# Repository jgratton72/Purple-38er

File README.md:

# 🟣 Purple-38er — ZX81+38 Clone (Rev 1.10)

A personal build of the **ZX81+38** clone using purple PCBs and tactile switch keys. This project documents the assembly, troubleshooting, and validation of a modern recreation of the Sinclair ZX81 using standard logic ICs and through-hole components.

---

## 🧰 Project Overview

- **Board Revision**: ZX81+38 Rev 1.10  
- **Design Origin**: Mahjongg’s open-source ZX81+38  
- **Build Variant**: Purple PCB with tactile switch keyboard  
- **Objective**: Achieve reliable boot with “K” prompt, stable composite video, and verified ROM/RAM operation

---

## 🔧 Key Components

| Component        | Value / Type             | Notes                                  |
|------------------|--------------------------|----------------------------------------|
| Crystal          | 13 MHz                   | Required for correct video timing      |
| CPU              | Z80A                     | Clocked at 3.25 MHz (÷4 from crystal)  |
| ROM              | 27C256 OTP EPROM         | One-time programmable; verified in chip tester |
| RAM              | HM62256BLP-7             | Stable operation confirmed             |
| RP2              | 22kΩ bussed network      | Pull-ups for D0–D7; critical for boot  |
| 74HCU04          | Unbuffered inverter      | Required for crystal oscillator        |

---

## 🧪 Troubleshooting Log

- **White Screen / No “K” Prompt**:
  - All chips tested in alternate board—confirmed working  
  - RP2 replaced with 22kΩ bussed network—resolved boot issue  
  - Clock verified: 13 MHz at 74HCU04 pin 2, 3.25 MHz at Z80 pin 6

- **ROM Activity**:
  - /CS and /OE toggling observed  
  - Address and data bus activity confirmed

- **Video Output**:
  - Composite waveform present at RCA jack  
  - Sync stable after oscillator validation

---

## 📝 Build Notes

- All decoupling capacitors (100 nF) installed near ICs  
- Socketed chips reseated during debugging  
- Board now boots reliably with “K” prompt and clean composite output

---

## 📷 Visuals

The `images/` folder contains a detailed visual archive of the design and build process:

| Subfolder            | Description                                                                 |
|----------------------|-----------------------------------------------------------------------------|
| `Assembly/`          | Final integration of keyboard and main PCB into the 3D-printed case         |
| `Case 3D/`           | 3D design views of the enclosure                                            |
| `Case Printed Raw/`  | Photos of the finished, unassembled printed case                            |
| `Keyboard 3D/`       | 3D renderings of the keyboard layout and switch matrix                      |
| `Keyboard Build/`    | Step-by-step documentation of keyboard assembly                             |
| `Keycaps/`           | Design files and visuals for custom keycaps                                 |
| `PCB 3D/`            | 3D views of the main PCB layout and component placement                     |
| `PCB Build/`         | Photo documentation of the main PCB assembly process                        |

---

## 🛠 Assembly Notes

- **USB Power Connector**:  
   Insulate the top of the USB connector to prevent contact with the underside of the tactile switches.

- **Capacitor C9**:  
  Angle C9 flat 90 degrees away from the main board to avoid shorting against the underside of the tactile switches.
  
  ⚠️ These issues caused keyboard failure when the case was closed.

---

## 📚 References

- [ZX81+38 Original Repository](https://github.com/mahjongg2/ZX81plus38)  
- [RevSpace Project Page](https://revspace.nl/ZX81plus38_simple_to_build_ZX-81_clone)  
- [Forum64 Build Threads](https://www.forum64.de)

---

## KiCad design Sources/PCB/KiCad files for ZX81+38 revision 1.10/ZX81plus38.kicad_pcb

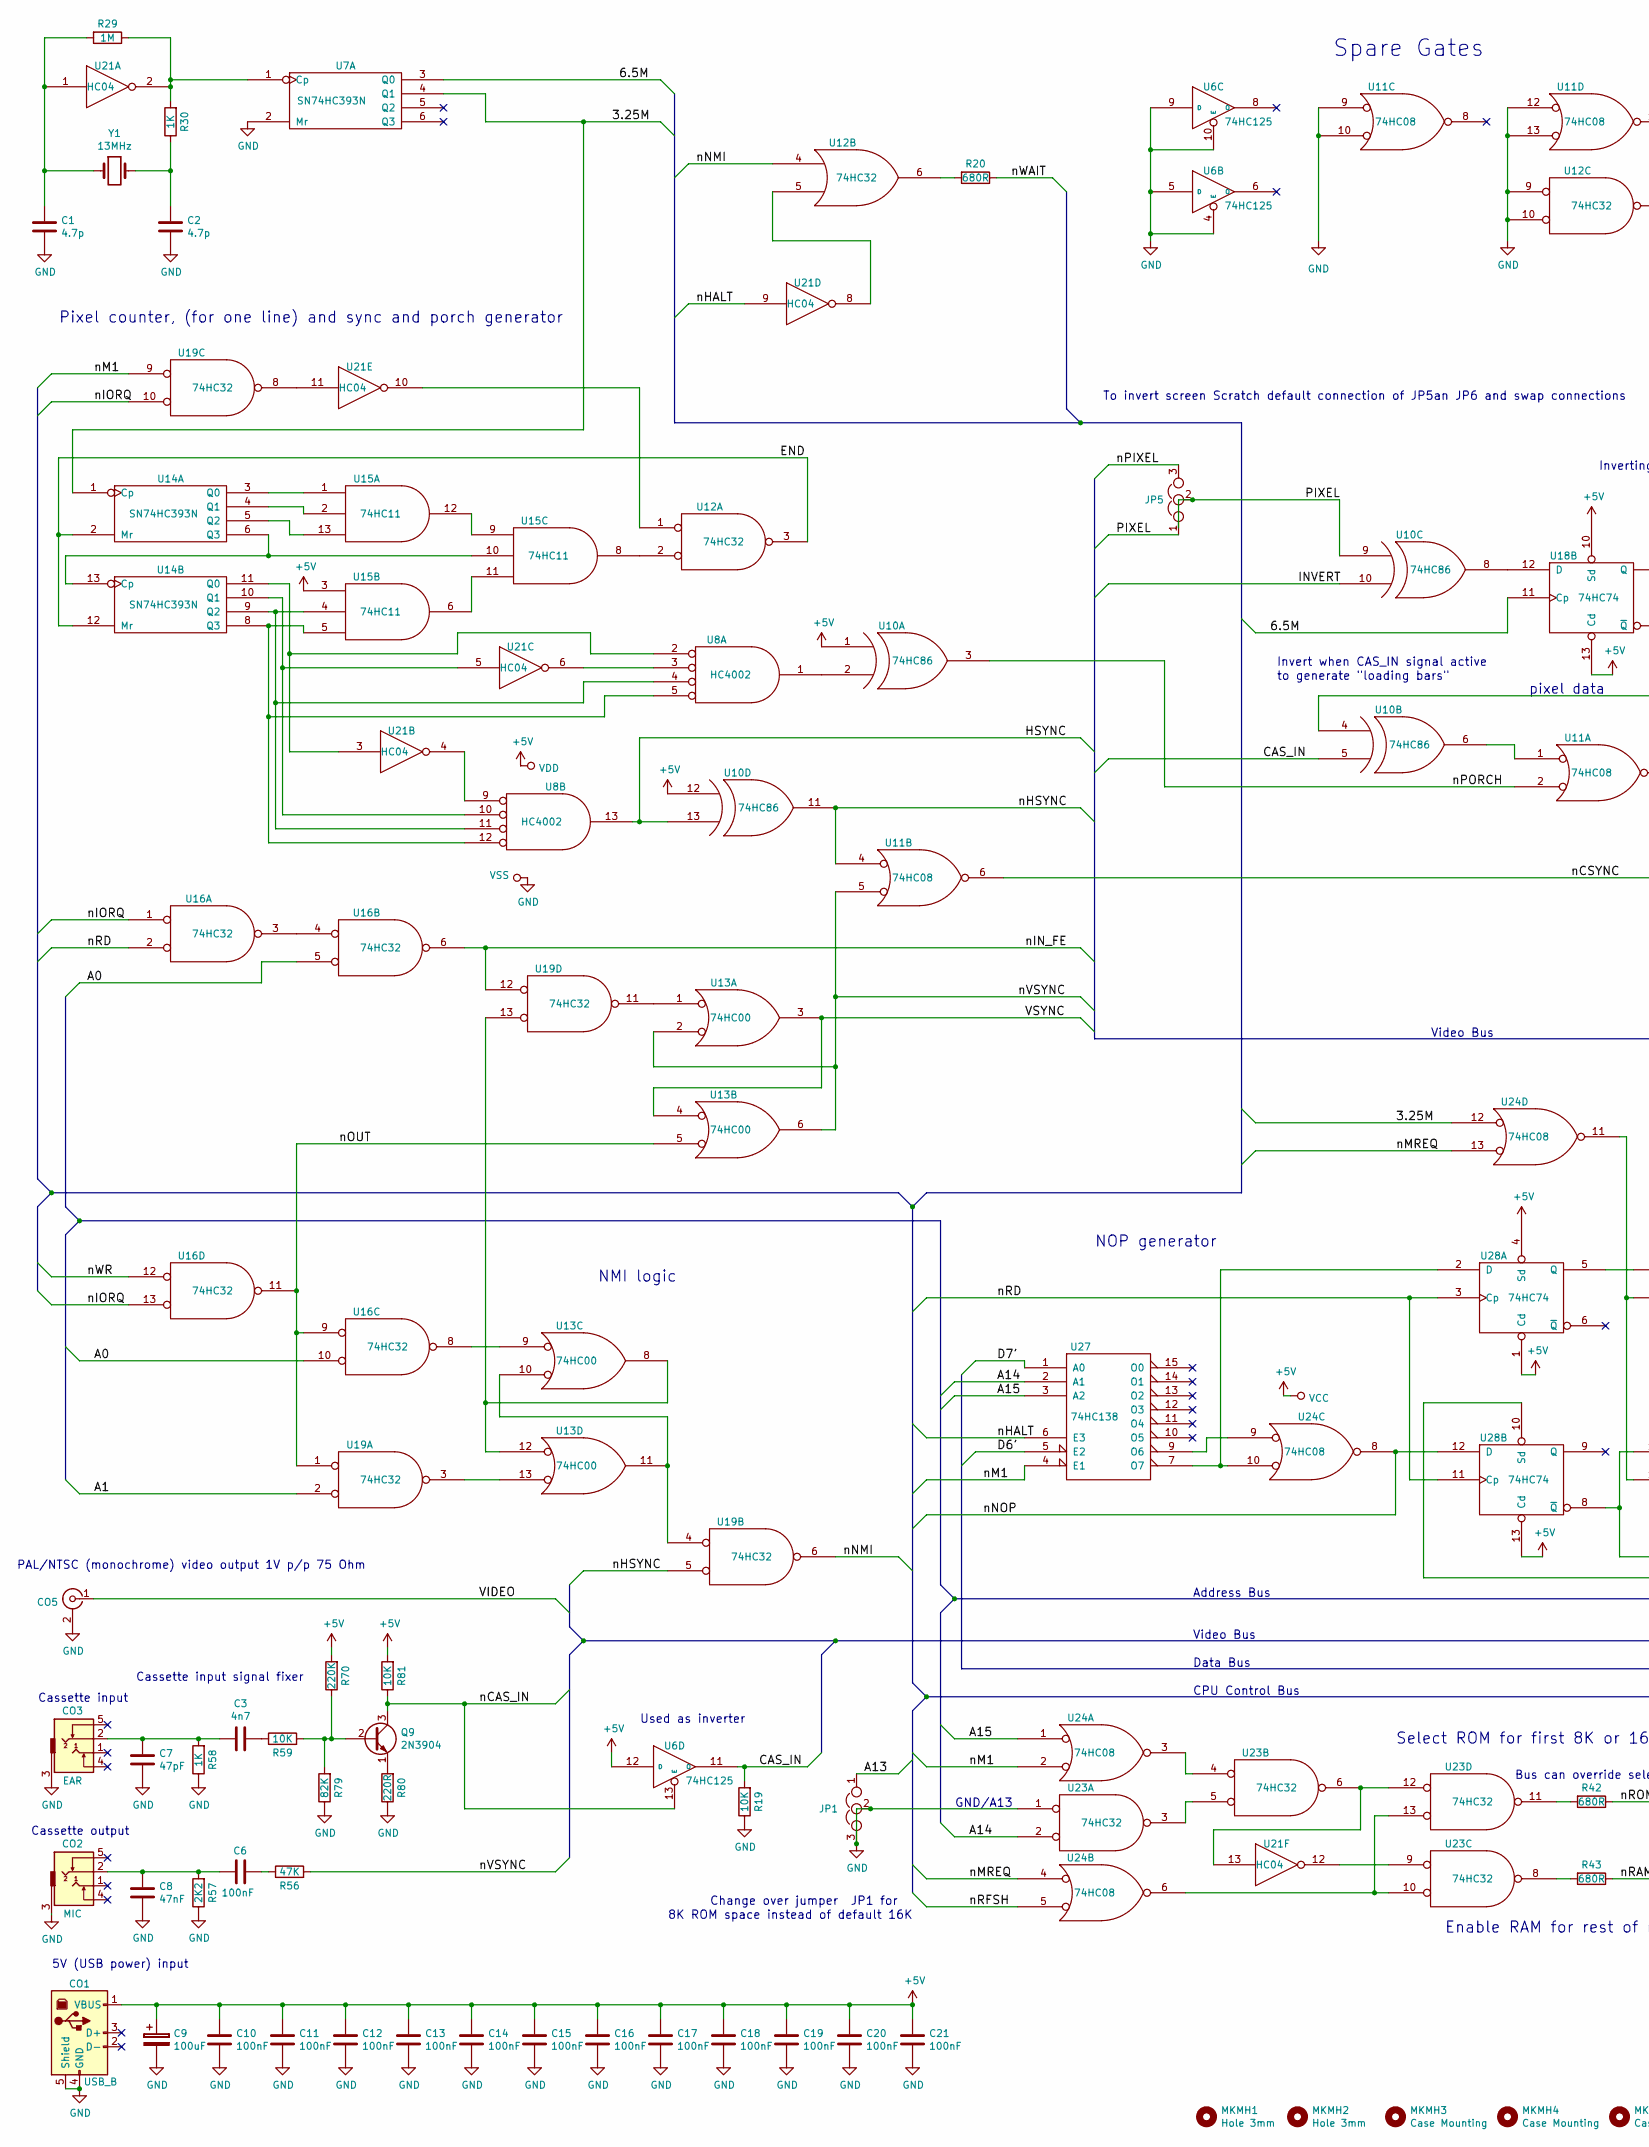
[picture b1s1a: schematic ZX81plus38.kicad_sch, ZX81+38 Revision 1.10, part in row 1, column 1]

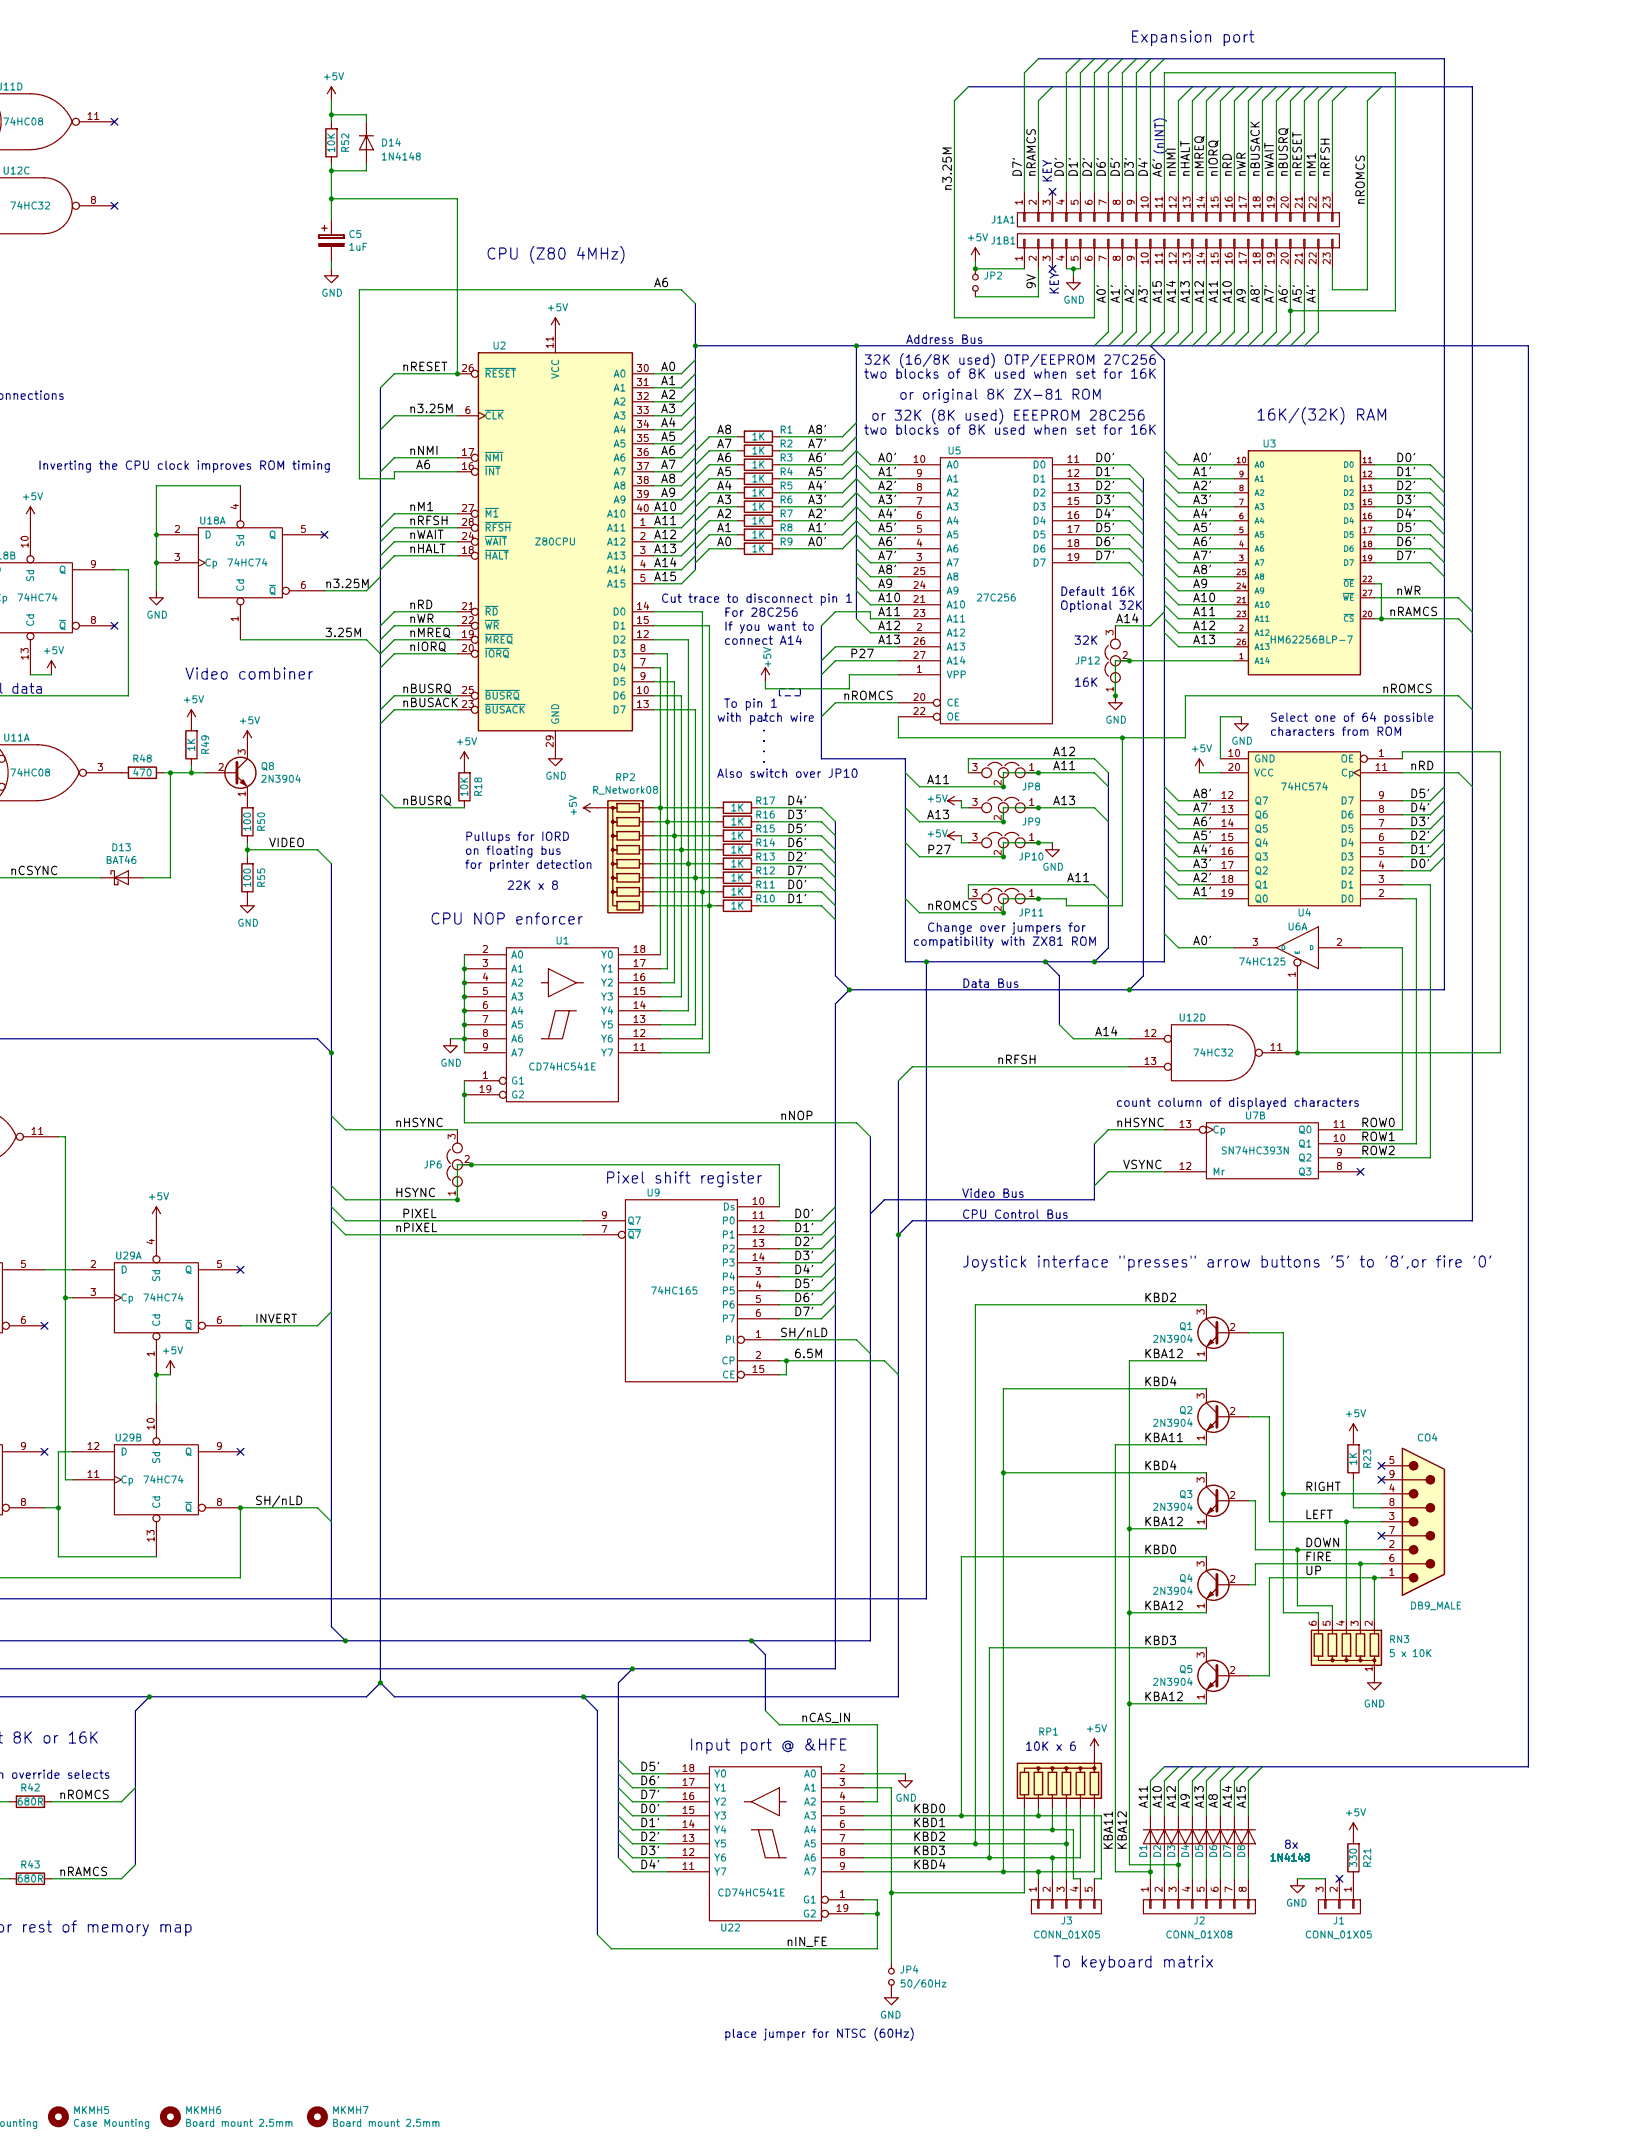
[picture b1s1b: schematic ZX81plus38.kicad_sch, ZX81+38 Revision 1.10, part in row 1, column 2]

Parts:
C1, C2: 4.7p; C_Disc_D3.0mm_W2.0mm_P2.50mm
C3: 4n7; C_Disc_D4.7mm_W2.5mm_P5.00mm
C5: 1uF; CP_Radial_Tantal_D6.0mm_P2.50mm
C6, C10, C11, C12, C13, C14, C15, C16, C17, C18, C19, C20, C21: 100nF; C_Disc_D4.7mm_W2.5mm_P5.00mm
C7: 47pF; C_Disc_D4.7mm_W2.5mm_P5.00mm
C8: 47nF; C_Disc_D4.7mm_W2.5mm_P5.00mm
C9: 100uF; CP_Radial_Tantal_D6.0mm_P2.50mm
CO1: USB_B
CO2: MIC; SPC21348
CO3: EAR; SPC21348
CO4: DB9_MALE; dB09-MALE
CO5: CONN_COAXIAL; RCA_CONNECTOR
D1, D2, D3, D4, D5, D6, D7, D8, D14: 1N4148; D_DO-35_SOD27_P7.62mm_Horizontal
D13: BAT46; D_DO-35_SOD27_P7.62mm_Horizontal
J1: CONN_01X05; Pin_Header_Straight_1x03_Pitch2.54mm
J1A1, J1B1: CONN_01X23; Pin_Header_Straight_1x23_Pitch2.54mm
J2: CONN_01X08; Pin_Header_Straight_1x08_Pitch2.54mm
J3: CONN_01X05; Pin_Header_Straight_1x05_Pitch2.54mm
JP1, JP5, JP6, JP8, JP9, JP10, JP11, JP12: Jumper_NC_Dual; Pin_Header_Straight_1x03_Pitch2.54mm
JP2: .; Pin_Header_Straight_1x02_Pitch2.54mm
JP4: 50/60Hz; Pin_Header_Straight_1x02_Pitch2.54mm
MKMH1, MKMH2: Hole 3mm; MountingHole_3.2mm_M3
MKMH3, MKMH4, MKMH5: Case Mounting; MountingHole_3.2mm_M3
MKMH6, MKMH7: Board mount 2.5mm; MountingHole_2.5mm
Q1, Q2, Q3, Q4, Q5, Q8, Q9: 2N3904; TO-92_Molded_Narrow
R1, R2, R3, R4, R5, R6, R7, R8, R9, R10, R11, R12, R13, R14, R15, R16, R17, R23, R58: 1K; R_Axial_DIN0204_L3.6mm_D1.6mm_P2.54mm_Vertical
R18, R19, R52, R59, R81: 10K; R_Axial_DIN0204_L3.6mm_D1.6mm_P2.54mm_Vertical
R20, R42, R43: 680R; R_Axial_DIN0204_L3.6mm_D1.6mm_P2.54mm_Vertical
R21: 330; R_Axial_DIN0207_L6.3mm_D2.5mm_P7.62mm_Horizontal
R29: 1M; R_Axial_DIN0207_L6.3mm_D2.5mm_P7.62mm_Horizontal
R30, R49: 1K; R_Axial_DIN0207_L6.3mm_D2.5mm_P7.62mm_Horizontal
R48: 470; R_Axial_DIN0207_L6.3mm_D2.5mm_P7.62mm_Horizontal
R50, R55: 100; R_Axial_DIN0207_L6.3mm_D2.5mm_P7.62mm_Horizontal
R56: 47K; R_Axial_DIN0204_L3.6mm_D1.6mm_P2.54mm_Vertical
R57: 2K2; R_Axial_DIN0204_L3.6mm_D1.6mm_P2.54mm_Vertical
R70: 220K; R_Axial_DIN0204_L3.6mm_D1.6mm_P2.54mm_Vertical
R79: 82K; R_Axial_DIN0204_L3.6mm_D1.6mm_P2.54mm_Vertical
R80: 220R; R_Axial_DIN0204_L3.6mm_D1.6mm_P2.54mm_Vertical
RN3: 5 x 10K; R_Array_SIP6
RP1: R_Network06; R_Array_SIP7
RP2: R_Network08; R_Array_SIP9
U1, U22: CD74HC541E; DIP-20_Ideal
U2: Z80CPU; DIP-40_ideal
U3: HM62256BLP-7; DIP-28_Ideal
U4: 74HC574; DIP-20_Ideal
U5: 27C256; DIP-28_Ideal
U6: 74HC125; DIP-14_Socket_Ideal
U7, U14: SN74HC393N; DIP-14_Socket_Ideal
U8: HC4002; DIP-14_Socket_Ideal
U9: 74HC165; DIP-16_Ideal
U10: 74HC86; DIP-14_Socket_Ideal
U11, U24: 74HC08; DIP-14_Socket_Ideal
U12, U16, U19, U23: 74HC32; DIP-14_Socket_Ideal
U13: 74HC00; DIP-14_Socket_Ideal
U15: 74HC11; DIP-14_Socket_Ideal
U18, U28, U29: 74HC74; DIP-14_Socket_Ideal
U21: HC04; DIP-14_Socket_Ideal
U27: 74HC138; DIP-16_Ideal
Y1: 13MHz; Crystal_SMD_HC49-SD

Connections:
+5V: C9.1, C10.2, C11.2, C12.2, C13.2, C14.2, C15.2, C16.2, C17.2, C18.2, C19.2, C20.2, C21.2, CO1.1 (VBUS), D14.1 (K), J1B1.1, JP2.1, JP9.3, JP10.3, Q8.3 (C), R18.2, R21.2, R23.2, R49.2, R52.2, R70.2, R81.2, RP1.1 (common), RP2.1 (common), U1.20 (VCC), U2.11 (VCC), U3.28 (VCC), U4.20 (VCC), U5.1 (VPP), U5.28 (VCC), U6.12 (D), U6.14 (VCC), U7.14 (VCC), U8.14 (VDD), U9.16 (VCC), U10.1 (IN1), U10.12 (IN1), U10.14 (VCC), U11.14 (VCC), U12.14 (VCC), U13.14 (VCC), U14.14 (VCC), U15.3, U15.14 (VCC), U16.14 (VCC), U18.10 (Sd), U18.13 (Cd), U18.14 (VCC), U19.14 (VCC), U21.14 (VCC), U22.20 (VCC), U23.14 (VCC), U24.14 (VCC), U27.16 (VCC), U28.1 (Cd), U28.4 (Sd), U28.13 (Cd), U28.14 (VCC), U29.1 (Cd), U29.4 (Sd), U29.10 (Sd), U29.14 (VCC)
/3.25M: U7.4 (Q1), U14.1 (Cp), U18.1 (Cd), U24.12
/6.5M: U7.3 (Q0), U9.2 (CP), U9.15 (CE), U18.11 (Cp)
/9V: J1B1.2, JP2.2
/A0: R9.2, U2.30 (A0), U16.5, U16.10
/A0': J1B1.7, R9.1, U3.10 (A0), U5.10 (A0), U6.3 (O)
/A1: R8.2, U2.31 (A1), U19.2
/A1': J1B1.8, R8.1, U3.9 (A1), U4.19 (Q0), U5.9 (A1)
/A2: R7.2, U2.32 (A2)
/A2': J1B1.9, R7.1, U3.8 (A2), U4.18 (Q1), U5.8 (A2)
/A3: R6.2, U2.33 (A3)
/A3': J1B1.10, R6.1, U3.7 (A3), U4.17 (Q2), U5.7 (A3)
/A4: R5.2, U2.34 (A4)
/A4': J1B1.22, R5.1, U3.6 (A4), U4.16 (Q3), U5.6 (A4)
/A5: R4.2, U2.35 (A5)
/A5': J1B1.21, R4.1, U3.5 (A5), U4.15 (Q4), U5.5 (A5)
/A6: R3.2, U2.16 (~INT), U2.36 (A6)
/A6': J1A1.11, J1B1.20, R3.1, U3.4 (A6), U4.14 (Q5), U5.4 (A6)
/A7: R2.2, U2.37 (A7)
/A7': J1B1.19, R2.1, U3.3 (A7), U4.13 (Q6), U5.3 (A7)
/A8: D6.1 (K), R1.2, U2.38 (A8)
/A8': J1B1.18, R1.1, U3.25 (A8), U4.12 (Q7), U5.25 (A8)
/A9: D4.1 (K), J1B1.17, U2.39 (A9), U3.24 (A9), U5.24 (A9)
/A10: D2.1 (K), J1B1.16, U2.40 (A10), U3.21 (A10), U5.21 (A10)
/A11: D1.1 (K), J1B1.15, JP8.1, JP8.2, JP11.3, U2.1 (A11), U3.23 (A11), U5.23 (A11)
/A12: D3.1 (K), J1B1.14, JP8.3, U2.2 (A12), U3.2 (A12), U5.2 (A12)
/A13: D5.1 (K), J1B1.13, JP1.1, JP9.1, JP9.2, U2.3 (A13), U3.26 (A13), U5.26 (A13)
/A14: D7.1 (K), J1B1.12, JP12.3, U2.4 (A14), U12.12, U23.2, U27.2 (A1)
/A15: D8.1 (K), J1B1.11, U2.5 (A15), U24.1, U27.3 (A2)
/CAS_IN: R19.2, U6.11 (O), U10.5 (IN2)
/D0': J1A1.4, R11.1, U3.11 (D0), U4.4 (D2), U5.11 (D0), U9.11 (P0), U22.15 (Y3)
/D1': J1A1.5, R10.1, U3.12 (D1), U4.5 (D3), U5.12 (D1), U9.12 (P1), U22.14 (Y4)
/D2': J1A1.6, R13.1, U3.13 (D2), U4.6 (D4), U5.13 (D2), U9.13 (P2), U22.13 (Y5)
/D3': J1A1.9, R16.1, U3.15 (D3), U4.7 (D5), U5.15 (D3), U9.14 (P3), U22.12 (Y6)
/D4': J1A1.10, R17.1, U3.16 (D4), U4.8 (D6), U5.16 (D4), U9.3 (P4), U22.11 (Y7)
/D5': J1A1.8, R15.1, U3.17 (D5), U4.9 (D7), U5.17 (D5), U9.4 (P5), U22.18 (Y0)
/D6': J1A1.7, R14.1, U3.18 (D6), U5.18 (D6), U9.5 (P6), U22.17 (Y1), U27.5 (E2)
/D7': J1A1.1, R12.1, U3.19 (D7), U5.19 (D7), U9.6 (P7), U22.16 (Y2), U27.1 (A0)
/DOWN: CO4.2, Q3.2 (B), RN3.5 (R4)
/END: U12.3, U14.2 (Mr), U14.12 (Mr)
/FIRE: CO4.6, Q4.2 (B), RN3.3 (R2)
/HSYNC: JP6.1, JP6.2, U8.13, U9.10 (Ds), U10.13 (IN2)
/INVERT: U10.10 (IN2), U29.6 (~Q)
/KBA11: D1.2 (A), J2.1, Q2.1 (E)
/KBA12: D3.2 (A), J2.3, Q1.1 (E), Q3.1 (E), Q4.1 (E), Q5.1 (E)
/KBD0: J3.5, Q4.3 (C), RP1.6 (R5), U22.5 (A3)
/KBD1: J3.4, RP1.5 (R4), U22.6 (A4)
/KBD2: J3.3, Q1.3 (C), RP1.4 (R3), U22.7 (A5)
/KBD3: J3.2, Q5.3 (C), RP1.3 (R2), U22.8 (A6)
/KBD4: J3.1, Q2.3 (C), Q3.3 (C), RP1.2 (R1), U22.9 (A7)
/LEFT: CO4.3, Q2.2 (B), RN3.4 (R3)
/PIXEL: JP5.1, JP5.2, U9.9 (Q7), U10.9 (IN1)
/RIGHT: CO4.4, Q1.2 (B), RN3.6 (R5)
/ROW0: U6.2 (D), U7.11 (Q0)
/ROW1: U4.2 (D0), U7.10 (Q1)
/ROW2: U4.3 (D1), U7.9 (Q2)
/SH/nLD: U9.1 (Pl), U28.10 (Sd), U29.8 (~Q)
/UP: CO4.1, Q5.2 (B), RN3.2 (R1)
/VIDEO: CO5.1 (In), R50.1, R55.2
/VSYNC: U7.12 (Mr), U13.3, U13.4
/n3.25M: J1B1.6, U2.6 (~CLK), U18.6 (~Q)
/nBUSACK: J1A1.18, U2.23 (~BUSACK)
/nBUSRQ: J1A1.20, R18.1, U2.25 (~BUSRQ)
/nCAS_IN: Q9.3 (C), R81.1, U6.13 (E), U22.4 (A2)
/nCSYNC: D13.1 (K), U11.6
/nHALT: J1A1.13, U2.18 (~HALT), U21.9, U27.6 (E3)
/nHSYNC: JP6.3, U7.13 (Cp), U10.11 (OUT), U11.4, U19.5
/nIN_FE: U16.6, U19.12, U22.1 (G1), U22.19 (G2)
/nIORQ: J1A1.15, U2.20 (~IORQ), U16.1, U16.13, U19.10
/nM1: J1A1.22, U2.27 (~M1), U19.9, U24.2, U27.4 (E1)
/nMREQ: J1A1.14, U2.19 (~MREQ), U24.4, U24.13
/nNMI: J1A1.12, U2.17 (~NMI), U12.4, U19.6
/nNOP: U1.1 (G1), U1.19 (G2), U24.8, U28.12 (D)
/nOUT: U13.5, U16.9, U16.11, U19.1
/nPIXEL: JP5.3, U9.7 (~Q7)
/nPORCH: U10.3 (OUT), U11.2
/nRAMCS: J1A1.2, R43.1, U3.20 (~CS), U3.22 (~OE)
/nRD: J1A1.16, U2.21 (~RD), U4.11 (Cp), U16.2, U28.3 (Cp), U28.11 (Cp)
/nRESET: C5.1, D14.2 (A), J1A1.21, R52.1, U2.26 (~RESET)
/nRFSH: J1A1.23, U2.28 (~RFSH), U12.13, U24.5
/nROMCS: J1B1.23, JP11.1, JP11.2, R42.1, U5.20 (CE), U5.22 (OE)
/nVSYNC: R56.2, U11.5, U13.2, U13.6
/nWAIT: J1A1.19, R20.1, U2.24 (~WAIT)
/nWR: J1A1.17, U2.22 (~WR), U3.27 (~WE), U16.12
GND: C1.2, C2.2, C5.2, C7.2, C8.2, C9.2, C10.1, C11.1, C12.1, C13.1, C14.1, C15.1, C16.1, C17.1, C18.1, C19.1, C20.1, C21.1, CO1.4 (GND), CO1.5 (Shield), CO2.3, CO3.3, CO5.2 (Ext), J1.3, J1B1.4, J1B1.5, JP1.2, JP1.3, JP4.2, JP10.1, JP10.2, JP12.1, JP12.2, R19.1, R55.1, R57.1, R58.1, R79.1, R80.1, RN3.1 (common), U1.2 (A0), U1.3 (A1), U1.4 (A2), U1.5 (A3), U1.6 (A4), U1.7 (A5), U1.8 (A6), U1.9 (A7), U1.10 (GND), U2.29 (GND), U3.1 (A14), U3.14 (GND), U4.10 (GND), U5.14 (GND), U5.27 (A14), U6.4 (E), U6.5 (D), U6.7 (GND), U6.9 (D), U6.10 (E), U7.2 (Mr), U7.7 (GND), U8.7 (VSS), U9.8 (GND), U10.7 (GND), U11.7 (GND), U11.9, U11.10, U11.12, U11.13, U12.7 (GND), U12.9, U12.10, U13.7 (GND), U14.7 (GND), U15.7 (GND), U16.7 (GND), U18.2 (D), U18.3 (Cp), U18.4 (Sd), U18.7 (GND), U19.7 (GND), U21.7 (GND), U22.2 (A0), U22.10 (GND), U23.1, U23.7 (GND), U24.7 (GND), U27.8 (GND), U28.7 (GND), U29.7 (GND)
unnamed: C1.1, R29.2, U21.1, Y1.1
unnamed: C2.1, R30.1, Y1.2
unnamed: C3.1, R59.1
unnamed: C3.2, C7.1, CO3.2, R58.2
unnamed: C6.1, R56.1
unnamed: C6.2, C8.1, CO2.2, R57.2
unnamed: CO4.8, R23.1
unnamed: D2.2 (A), J2.2
unnamed: D4.2 (A), J2.4
unnamed: D5.2 (A), J2.5
unnamed: D6.2 (A), J2.6
unnamed: D7.2 (A), J2.7
unnamed: D8.2 (A), J2.8
unnamed: D13.2 (A), Q8.2 (B), R48.1, R49.1
unnamed: J1.1, R21.1
unnamed: JP4.1, RP1.7 (R6), U22.3 (A1)
unnamed: Q8.1 (E), R50.2
unnamed: Q9.1 (E), R80.2
unnamed: Q9.2 (B), R59.2, R70.1, R79.2
unnamed: R10.2, RP2.9 (R8), U1.11 (Y7), U2.15 (D1)
unnamed: R11.2, RP2.8 (R7), U1.12 (Y6), U2.14 (D0)
unnamed: R12.2, RP2.7 (R6), U1.13 (Y5), U2.13 (D7)
unnamed: R13.2, RP2.6 (R5), U1.14 (Y4), U2.12 (D2)
unnamed: R14.2, RP2.5 (R4), U1.15 (Y3), U2.10 (D6)
unnamed: R15.2, RP2.4 (R3), U1.16 (Y2), U2.9 (D5)
unnamed: R16.2, RP2.3 (R2), U1.17 (Y1), U2.8 (D3)
unnamed: R17.2, RP2.2 (R1), U1.18 (Y0), U2.7 (D4)
unnamed: R20.2, U12.6
unnamed: R29.1, R30.2, U7.1 (Cp), U21.2
unnamed: R42.2, U23.11
unnamed: R43.2, U23.8
unnamed: R48.2, U11.3
unnamed: U8.1, U10.2 (IN2)
unnamed: U10.4 (IN1), U18.9 (Q)
unnamed: U10.6 (OUT), U11.1
unnamed: U10.8 (OUT), U18.12 (D)
unnamed: U12.1, U21.10
unnamed: U12.2, U15.8
unnamed: U12.5, U21.8
unnamed: U4.1 (OE), U6.1 (E), U12.11
unnamed: U13.1, U19.11
unnamed: U13.9, U16.8
unnamed: U13.10, U13.11, U19.4
unnamed: U13.8, U13.12, U19.13
unnamed: U13.13, U19.3
unnamed: U14.3 (Q0), U15.1
unnamed: U14.4 (Q1), U15.2
unnamed: U14.5 (Q2), U15.13
unnamed: U8.5, U8.12, U14.8 (Q3), U15.5
unnamed: U8.4, U8.11, U14.9 (Q2), U15.4
unnamed: U8.10, U14.10 (Q1), U21.5
unnamed: U8.2, U14.11 (Q0), U21.3
unnamed: U14.6 (Q3), U14.13 (Cp), U15.10
unnamed: U15.6, U15.11
unnamed: U15.9, U15.12
unnamed: U16.3, U16.4
unnamed: U19.8, U21.11
unnamed: U8.9, U21.4
unnamed: U8.3, U21.6
unnamed: U21.12, U23.9
unnamed: U21.13, U23.6, U23.12
unnamed: U23.3, U23.5
unnamed: U23.4, U24.3
unnamed: U23.10, U23.13, U24.6
unnamed: U24.9, U27.9 (O6)
unnamed: U24.10, U27.7 (O7), U28.2 (D)
unnamed: U24.11, U29.3 (Cp), U29.11 (Cp)
unnamed: U28.5 (Q), U29.2 (D)
unnamed: U28.8 (~Q), U29.12 (D), U29.13 (Cd)

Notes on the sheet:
Expansion port
Inverting the CPU clock improves ROM timing
32K (16/8K used) OTP/EEPROM 27C256
Change over jumpers for
Also switch over JP10
to generate "loading bars"
Address Bus
Address Bus
Used as inverter
16K
count column of displayed characters
pixel data
NMI logic
To invert screen Scratch default connection of JP5an JP6 and swap connections
KEY
Cut trace to disconnect pin 1
Select ROM for first 8K or 16K
. . . . .
Cassette input
Data Bus
Bus can override selects
22K x 8
or 32K (8K used) EEEPROM 28C256
Select one of 64 possible
NOP generator
10K x 6
32K
CPU NOP enforcer
with patch wire
Video Bus
GND/A13
for printer detection
CPU Control Bus
CPU (Z80 4MHz)
place jumper for NTSC (60Hz)
Pullups for IORD
For 28C256
two blocks of 8K used when set for 16K
5V (USB power) input
on floating bus

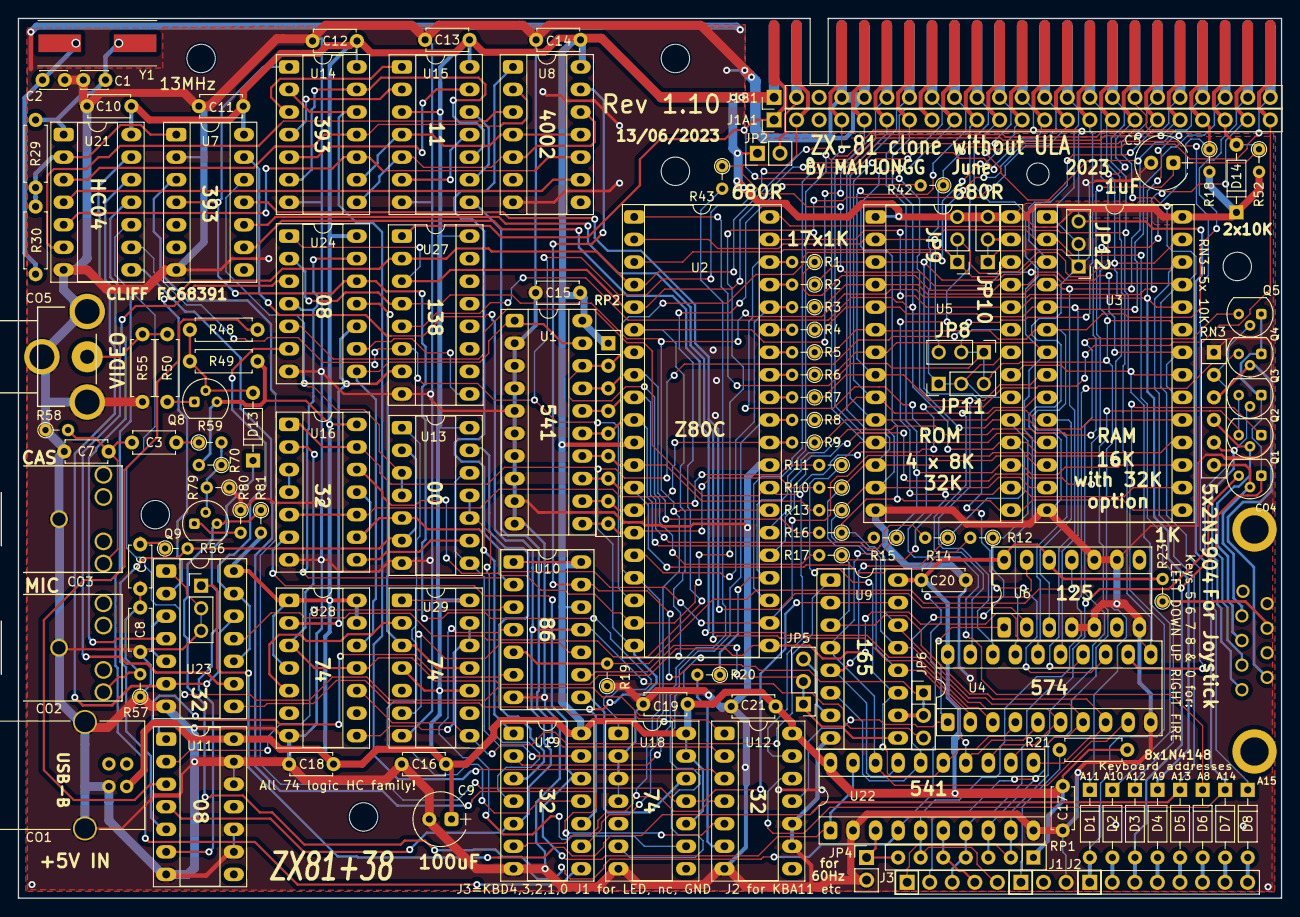
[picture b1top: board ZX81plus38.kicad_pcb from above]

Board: 2 copper layers, 142.2 x 99.1 mm, 132 parts (0 on the bottom side), 154 nets.

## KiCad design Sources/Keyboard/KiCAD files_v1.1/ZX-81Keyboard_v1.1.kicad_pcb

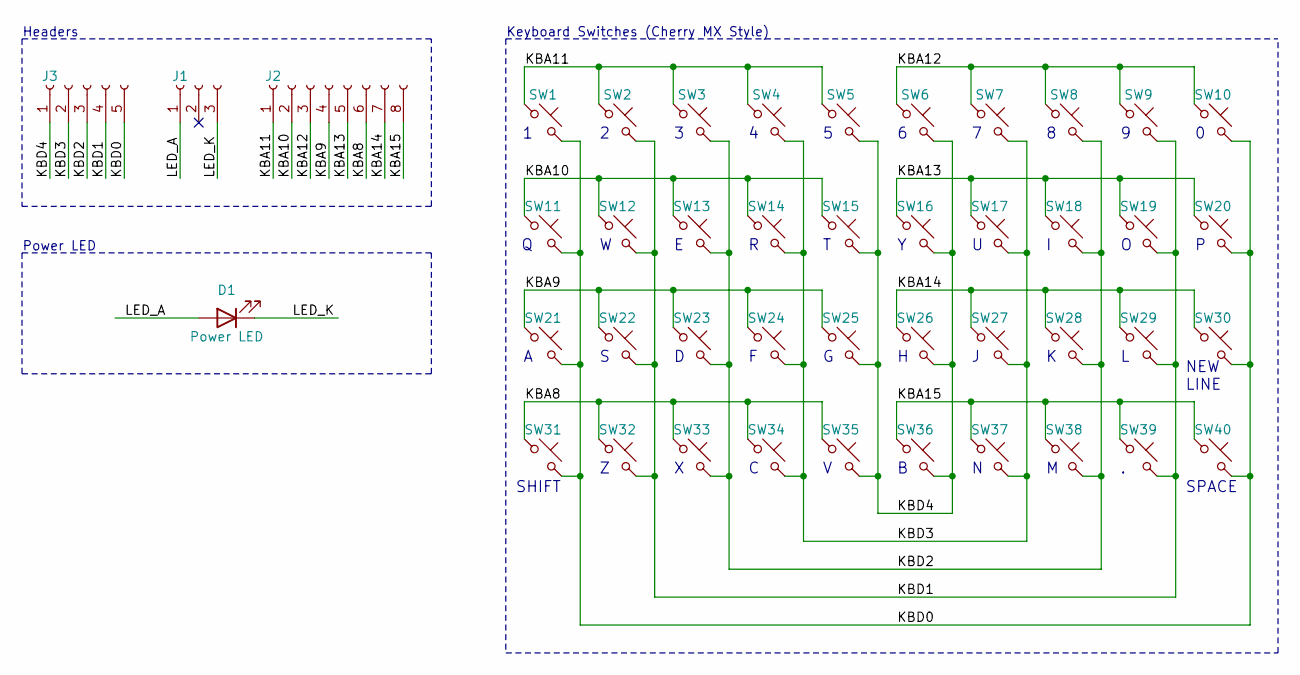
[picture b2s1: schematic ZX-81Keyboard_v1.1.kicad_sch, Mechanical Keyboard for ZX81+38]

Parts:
D1: Power LED; LED_1206_3216Metric_Pad1.42x1.75mm_HandSolder
J1: Conn_01x03_Female; PinSocket_1x03_P2.54mm_Vertical
J2: Conn_01x08_Female; PinSocket_1x08_P2.54mm_Vertical
J3: Conn_01x05_Female; PinSocket_1x05_P2.54mm_Vertical
SW1: 1; SW_Cherry_MX_1.00u_PCB
SW2: 2; SW_Cherry_MX_1.00u_PCB
SW3: 3; SW_Cherry_MX_1.00u_PCB
SW4: 4; SW_Cherry_MX_1.00u_PCB
SW5: 5; SW_Cherry_MX_1.00u_PCB
SW6: 6; SW_Cherry_MX_1.00u_PCB
SW7: 7; SW_Cherry_MX_1.00u_PCB
SW8: 8; SW_Cherry_MX_1.00u_PCB
SW9: 9; SW_Cherry_MX_1.00u_PCB
SW10: 0; SW_Cherry_MX_1.00u_PCB
SW11: Q; SW_Cherry_MX_1.00u_PCB
SW12: W; SW_Cherry_MX_1.00u_PCB
SW13: E; SW_Cherry_MX_1.00u_PCB
SW14: R; SW_Cherry_MX_1.00u_PCB
SW15: T; SW_Cherry_MX_1.00u_PCB
SW16: Y; SW_Cherry_MX_1.00u_PCB
SW17: U; SW_Cherry_MX_1.00u_PCB
SW18: I; SW_Cherry_MX_1.00u_PCB
SW19: O; SW_Cherry_MX_1.00u_PCB
SW20: P; SW_Cherry_MX_1.00u_PCB
SW21: A; SW_Cherry_MX_1.00u_PCB
SW22: S; SW_Cherry_MX_1.00u_PCB
SW23: D; SW_Cherry_MX_1.00u_PCB
SW24: F; SW_Cherry_MX_1.00u_PCB
SW25: G; SW_Cherry_MX_1.00u_PCB
SW26: H; SW_Cherry_MX_1.00u_PCB
SW27: J; SW_Cherry_MX_1.00u_PCB
SW28: K; SW_Cherry_MX_1.00u_PCB
SW29: L; SW_Cherry_MX_1.00u_PCB
SW30: NEW LINE; SW_Cherry_MX_1.00u_PCB
SW31: SHIFT; SW_Cherry_MX_1.00u_PCB
SW32: Z; SW_Cherry_MX_1.00u_PCB
SW33: X; SW_Cherry_MX_1.00u_PCB
SW34: C; SW_Cherry_MX_1.00u_PCB
SW35: V; SW_Cherry_MX_1.00u_PCB
SW36: B; SW_Cherry_MX_1.00u_PCB
SW37: N; SW_Cherry_MX_1.00u_PCB
SW38: M; SW_Cherry_MX_1.00u_PCB
SW39: .; SW_Cherry_MX_1.00u_PCB
SW40: SPACE; SW_Cherry_MX_1.00u_PCB

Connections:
/KBA8: J2.6, SW31.1, SW32.1, SW33.1, SW34.1, SW35.1
/KBA9: J2.4, SW21.1, SW22.1, SW23.1, SW24.1, SW25.1
/KBA10: J2.2, SW11.1, SW12.1, SW13.1, SW14.1, SW15.1
/KBA11: J2.1, SW1.1, SW2.1, SW3.1, SW4.1, SW5.1
/KBA12: J2.3, SW6.1, SW7.1, SW8.1, SW9.1, SW10.1
/KBA13: J2.5, SW16.1, SW17.1, SW18.1, SW19.1, SW20.1
/KBA14: J2.7, SW26.1, SW27.1, SW28.1, SW29.1, SW30.1
/KBA15: J2.8, SW36.1, SW37.1, SW38.1, SW39.1, SW40.1
/KBD0: J3.5, SW1.2, SW10.2, SW11.2, SW20.2, SW21.2, SW30.2, SW31.2, SW40.2
/KBD1: J3.4, SW2.2, SW9.2, SW12.2, SW19.2, SW22.2, SW29.2, SW32.2, SW39.2
/KBD2: J3.3, SW3.2, SW8.2, SW13.2, SW18.2, SW23.2, SW28.2, SW33.2, SW38.2
/KBD3: J3.2, SW4.2, SW7.2, SW14.2, SW17.2, SW24.2, SW27.2, SW34.2, SW37.2
/KBD4: J3.1, SW5.2, SW6.2, SW15.2, SW16.2, SW25.2, SW26.2, SW35.2, SW36.2
/LED_A: D1.2 (A), J1.1
/LED_K: D1.1 (K), J1.3

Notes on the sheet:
SPACE
Headers
SHIFT
Power LED
NEW LINE
Keyboard Switches (Cherry MX Style)

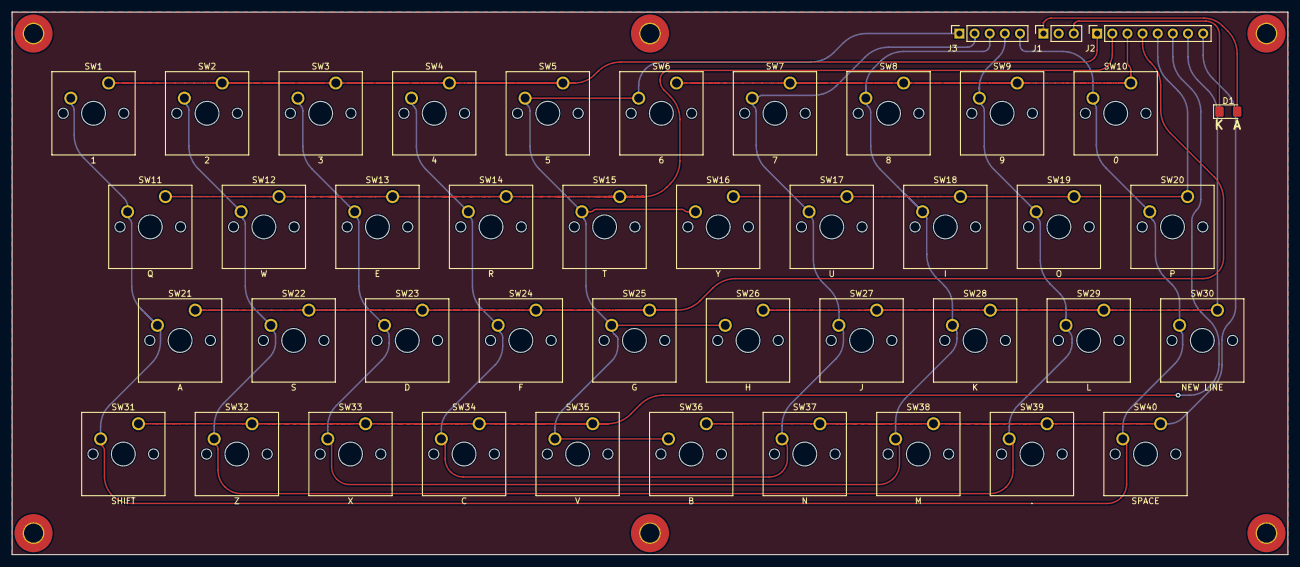
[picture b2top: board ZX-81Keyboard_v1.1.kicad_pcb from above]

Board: 2 copper layers, 214.0 x 91.0 mm, 44 parts (0 on the bottom side), 15 nets.

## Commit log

2025-08-02 added 3D case models
2025-08-09 adde iBOM
2025-08-10 Add files via upload
    Nearly there.
    Ordered some caps to make it right.
    I have some but the footprint isn’t correct and want it to be right.
2025-08-14 new iBOM with pads
2025-08-17 Create Assembly
